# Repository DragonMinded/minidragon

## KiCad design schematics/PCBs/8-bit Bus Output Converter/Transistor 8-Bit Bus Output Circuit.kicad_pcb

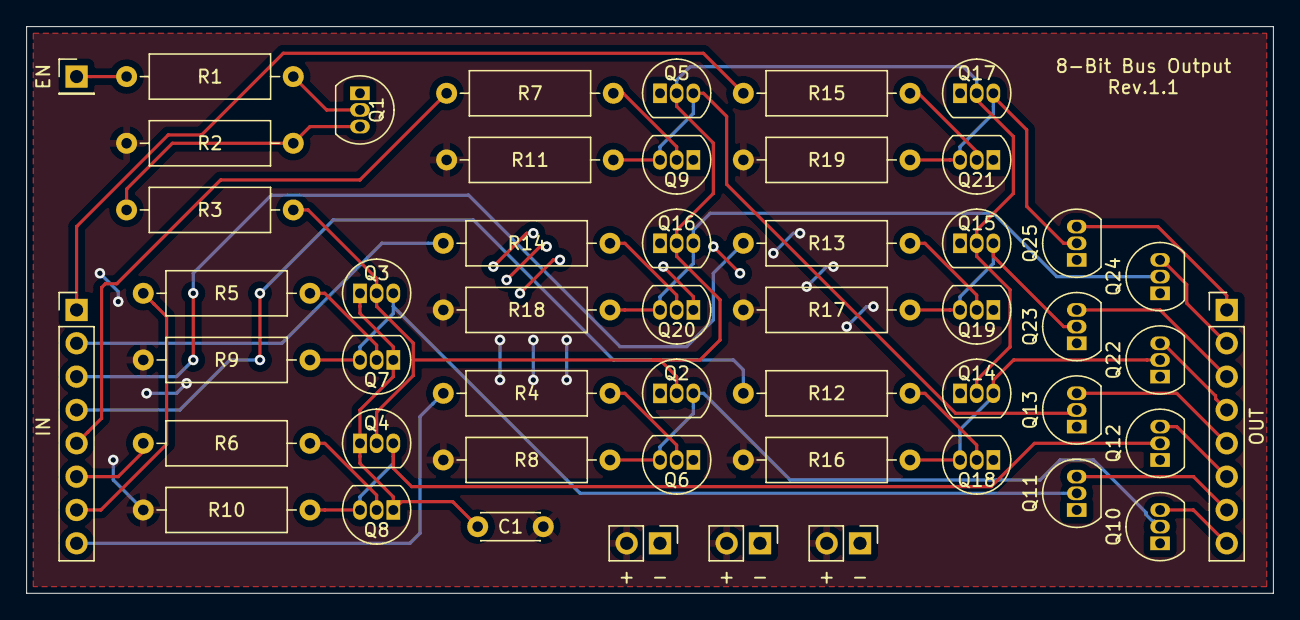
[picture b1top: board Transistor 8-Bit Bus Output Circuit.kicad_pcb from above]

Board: 2 copper layers, 95.0 x 43.2 mm, 51 parts (0 on the bottom side), 38 nets.

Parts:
C1: 0.1uF; C_Disc_D4.3mm_W1.9mm_P5.00mm
J1: EN; PinHeader_1x01_P2.54mm_Vertical
J2: IN; PinHeader_1x08_P2.54mm_Vertical
J3: OUT; PinHeader_1x08_P2.54mm_Vertical
J4, J5, J6: Power; PinHeader_1x02_P2.54mm_Vertical
Q1, Q2, Q3, Q4, Q5, Q6, Q7, Q8, Q9, Q10, Q11, Q12, Q13, Q14, Q15, Q16, Q17, Q18, Q19, Q20, Q21, Q22, Q23, Q24, Q25: 2N2222; TO-92_Inline
R1, R4, R5, R6, R7, R12, R13, R14, R15: 10K; R_Axial_DIN0309_L9.0mm_D3.2mm_P12.70mm_Horizontal
R2, R8, R9, R10, R11, R16, R17, R18, R19: 1K; R_Axial_DIN0309_L9.0mm_D3.2mm_P12.70mm_Horizontal
R3: 100; R_Axial_DIN0309_L9.0mm_D3.2mm_P12.70mm_Horizontal

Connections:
GND: C1.2, J4.1, J5.1, J6.1, Q1.1 (E), Q2.1 (E), Q3.1 (E), Q4.1 (E), Q5.1 (E), Q6.1 (E), Q7.1 (E), Q8.1 (E), Q9.1 (E), Q10.1 (E), Q11.1 (E), Q12.1 (E), Q13.1 (E), Q14.1 (E), Q15.1 (E), Q16.1 (E), Q17.1 (E), Q18.1 (E), Q19.1 (E), Q20.1 (E), Q21.1 (E), Q22.1 (E), Q23.1 (E), Q24.1 (E), Q25.1 (E)
unnamed: J1.1, R1.2
unnamed: J2.1, R15.2
unnamed: J2.2, R14.2
unnamed: J2.3, R13.2
unnamed: J2.4, R12.2
unnamed: J2.5, R7.2
unnamed: J2.6, R6.2
unnamed: J2.7, R5.2
unnamed: J2.8, R4.2
unnamed: J3.1, Q25.3 (C)
unnamed: J3.2, Q24.3 (C)
unnamed: J3.3, Q23.3 (C)
unnamed: J3.4, Q22.3 (C)
unnamed: J3.5, Q13.3 (C)
unnamed: J3.6, Q12.3 (C)
unnamed: J3.7, Q11.3 (C)
unnamed: J3.8, Q10.3 (C)
unnamed: Q1.2 (B), R1.1
unnamed: Q1.3 (C), R2.1, R3.2
unnamed: Q6.2 (B), R4.1
unnamed: Q7.2 (B), R5.1
unnamed: Q8.2 (B), R6.1
unnamed: Q9.2 (B), R7.1
unnamed: Q2.3 (C), Q6.3 (C), Q10.2 (B), R8.1
unnamed: Q3.3 (C), Q7.3 (C), Q11.2 (B), R9.1
unnamed: Q4.3 (C), Q8.3 (C), Q12.2 (B), R10.1
unnamed: Q5.3 (C), Q9.3 (C), Q13.2 (B), R11.1
unnamed: Q2.2 (B), Q3.2 (B), Q4.2 (B), Q5.2 (B), Q14.2 (B), Q15.2 (B), Q16.2 (B), Q17.2 (B), R3.1
unnamed: Q14.3 (C), Q18.3 (C), Q22.2 (B), R16.1
unnamed: Q15.3 (C), Q19.3 (C), Q23.2 (B), R17.1
unnamed: Q16.3 (C), Q20.3 (C), Q24.2 (B), R18.1
unnamed: Q17.3 (C), Q21.3 (C), Q25.2 (B), R19.1
unnamed: Q18.2 (B), R12.1
unnamed: Q19.2 (B), R13.1
unnamed: Q20.2 (B), R14.1
unnamed: Q21.2 (B), R15.1
VCC: C1.1, J4.2, J5.2, J6.2, R2.2, R8.2, R9.2, R10.2, R11.2, R16.2, R17.2, R18.2, R19.2

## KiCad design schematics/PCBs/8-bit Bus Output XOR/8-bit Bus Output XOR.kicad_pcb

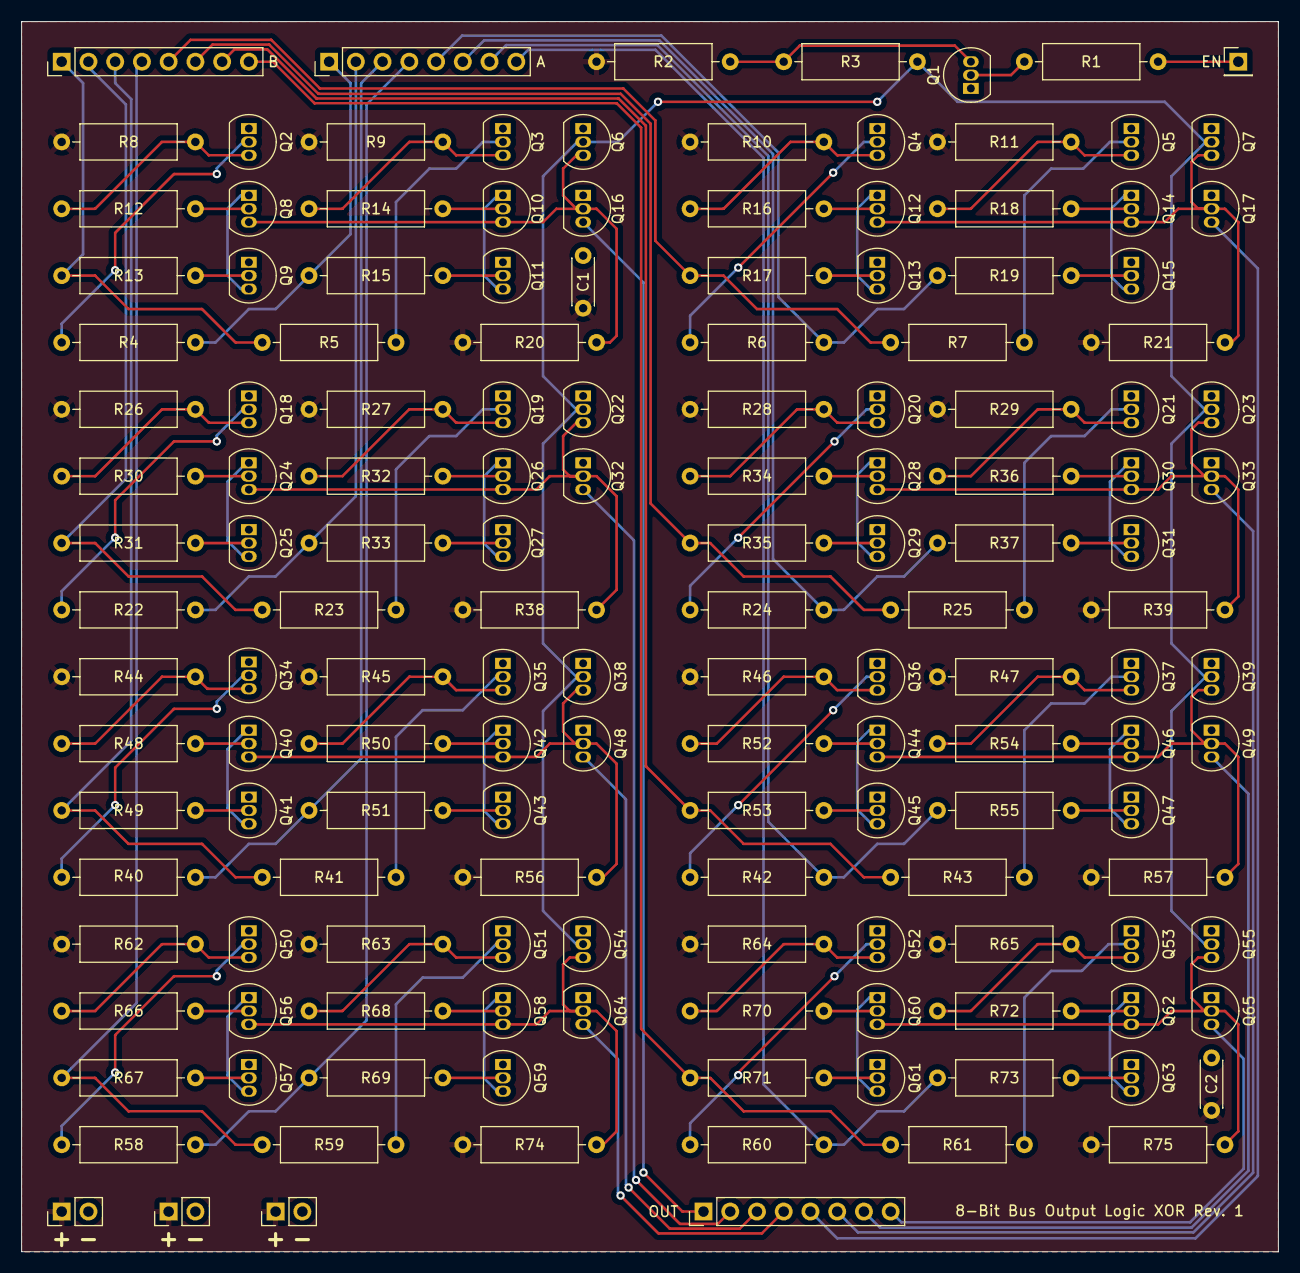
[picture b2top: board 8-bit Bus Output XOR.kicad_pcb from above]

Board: 2 copper layers, 119.4 x 116.8 mm, 149 parts (0 on the bottom side), 118 nets.

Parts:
C1, C2: 0.1uF; C_Disc_D4.3mm_W1.9mm_P5.00mm
J1: EN; PinHeader_1x01_P2.54mm_Vertical
J2: A; PinHeader_1x08_P2.54mm_Vertical
J3: B; PinHeader_1x08_P2.54mm_Vertical
J4: OUT; PinHeader_1x08_P2.54mm_Vertical
J5, J6, J7: POWER; PinHeader_1x02_P2.54mm_Vertical
Q1, Q2, Q3, Q4, Q5, Q6, Q7, Q8, Q9, Q10, Q11, Q12, Q13, Q14, Q15, Q16, Q17, Q18, Q19, Q20, Q21, Q22, Q23, Q24, Q25, Q26, Q27, Q28, Q29, Q30, Q31, Q32, Q33, Q34, Q35, Q36, Q37, Q38, Q39, Q40, Q41, Q42, Q43, Q44, Q45, Q46, Q47, Q48, Q49, Q50, Q51, Q52, Q53, Q54, Q55, Q56, Q57, Q58, Q59, Q60, Q61, Q62, Q63, Q64, Q65: 2N2222; TO-92_Inline
R1, R4, R5, R6, R7, R12, R13, R14, R15, R16, R17, R18, R19, R22, R23, R24, R25, R30, R31, R32, R33, R34, R35, R36, R37, R40, R41, R42, R43, R48, R49, R50, R51, R52, R53, R54, R55, R58, R59, R60, R61, R66, R67, R68, R69, R70, R71, R72, R73: 10K; R_Axial_DIN0309_L9.0mm_D3.2mm_P12.70mm_Horizontal
R2, R8, R9, R10, R11, R20, R21, R26, R27, R28, R29, R38, R39, R44, R45, R46, R47, R56, R57, R62, R63, R64, R65, R74, R75: 1K; R_Axial_DIN0309_L9.0mm_D3.2mm_P12.70mm_Horizontal
R3: 100; R_Axial_DIN0309_L9.0mm_D3.2mm_P12.70mm_Horizontal

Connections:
/A1: J2.1, R4.2, R15.2
/A2: J2.2, R22.2, R33.2
/A3: J2.3, R40.2, R51.2
/A4: J2.4, R58.2, R69.2
/A5: J2.5, R6.2, R19.2
/A6: J2.6, R24.2, R37.2
/A7: J2.7, R42.2, R55.2
/A8: J2.8, R60.2, R73.2
/B1: J3.1, R5.2, R13.2
/B2: J3.2, R23.2, R31.2
/B3: J3.3, R41.2, R49.2
/B4: J3.4, R59.2, R67.2
/B5: J3.5, R7.2, R17.2
/B6: J3.6, R25.2, R35.2
/B7: J3.7, R43.2, R53.2
/B8: J3.8, R61.2, R71.2
/EN_INT: Q6.2 (B), Q7.2 (B), Q22.2 (B), Q23.2 (B), Q38.2 (B), Q39.2 (B), Q54.2 (B), Q55.2 (B), R3.1
/O1: J4.1, Q16.3 (C)
/O2: J4.2, Q32.3 (C)
/O3: J4.3, Q48.3 (C)
/O4: J4.4, Q64.3 (C)
/O5: J4.5, Q17.3 (C)
/O6: J4.6, Q33.3 (C)
/O7: J4.7, Q49.3 (C)
/O8: J4.8, Q65.3 (C)
GND: C1.2, C2.2, J5.2, J6.2, J7.2, Q1.1 (E), Q2.1 (E), Q3.1 (E), Q4.1 (E), Q5.1 (E), Q6.1 (E), Q7.1 (E), Q9.1 (E), Q11.1 (E), Q13.1 (E), Q15.1 (E), Q16.1 (E), Q17.1 (E), Q18.1 (E), Q19.1 (E), Q20.1 (E), Q21.1 (E), Q22.1 (E), Q23.1 (E), Q25.1 (E), Q27.1 (E), Q29.1 (E), Q31.1 (E), Q32.1 (E), Q33.1 (E), Q34.1 (E), Q35.1 (E), Q36.1 (E), Q37.1 (E), Q38.1 (E), Q39.1 (E), Q41.1 (E), Q43.1 (E), Q45.1 (E), Q47.1 (E), Q48.1 (E), Q49.1 (E), Q50.1 (E), Q51.1 (E), Q52.1 (E), Q53.1 (E), Q54.1 (E), Q55.1 (E), Q57.1 (E), Q59.1 (E), Q61.1 (E), Q63.1 (E), Q64.1 (E), Q65.1 (E)
unnamed: J1.1, R1.2
unnamed: Q1.2 (B), R1.1
unnamed: Q1.3 (C), R2.1, R3.2
unnamed: Q2.2 (B), R4.1
unnamed: Q2.3 (C), R8.2, R12.2
unnamed: Q3.2 (B), R5.1
unnamed: Q3.3 (C), R9.2, R14.2
unnamed: Q4.2 (B), R6.1
unnamed: Q4.3 (C), R10.2, R16.2
unnamed: Q5.2 (B), R7.1
unnamed: Q5.3 (C), R11.2, R18.2
unnamed: Q8.2 (B), R12.1
unnamed: Q8.1 (E), Q9.3 (C)
unnamed: Q9.2 (B), R13.1
unnamed: Q10.2 (B), R14.1
unnamed: Q6.3 (C), Q8.3 (C), Q10.3 (C), Q16.2 (B), R20.1
unnamed: Q10.1 (E), Q11.3 (C)
unnamed: Q11.2 (B), R15.1
unnamed: Q12.2 (B), R16.1
unnamed: Q7.3 (C), Q12.3 (C), Q14.3 (C), Q17.2 (B), R21.1
unnamed: Q12.1 (E), Q13.3 (C)
unnamed: Q13.2 (B), R17.1
unnamed: Q14.2 (B), R18.1
unnamed: Q14.1 (E), Q15.3 (C)
unnamed: Q15.2 (B), R19.1
unnamed: Q18.2 (B), R22.1
unnamed: Q18.3 (C), R26.2, R30.2
unnamed: Q19.2 (B), R23.1
unnamed: Q19.3 (C), R27.2, R32.2
unnamed: Q20.2 (B), R24.1
unnamed: Q20.3 (C), R28.2, R34.2
unnamed: Q21.2 (B), R25.1
unnamed: Q21.3 (C), R29.2, R36.2
unnamed: Q22.3 (C), Q24.3 (C), Q26.3 (C), Q32.2 (B), R38.1
unnamed: Q23.3 (C), Q28.3 (C), Q30.3 (C), Q33.2 (B), R39.1
unnamed: Q24.2 (B), R30.1
unnamed: Q24.1 (E), Q25.3 (C)
unnamed: Q25.2 (B), R31.1
unnamed: Q26.2 (B), R32.1
unnamed: Q26.1 (E), Q27.3 (C)
unnamed: Q27.2 (B), R33.1
unnamed: Q28.2 (B), R34.1
unnamed: Q28.1 (E), Q29.3 (C)
unnamed: Q29.2 (B), R35.1
unnamed: Q30.2 (B), R36.1
unnamed: Q30.1 (E), Q31.3 (C)
unnamed: Q31.2 (B), R37.1
unnamed: Q34.2 (B), R40.1
unnamed: Q34.3 (C), R44.2, R48.2
unnamed: Q35.2 (B), R41.1
unnamed: Q35.3 (C), R45.2, R50.2
unnamed: Q36.2 (B), R42.1
unnamed: Q36.3 (C), R46.2, R52.2
unnamed: Q37.2 (B), R43.1
unnamed: Q37.3 (C), R47.2, R54.2
unnamed: Q38.3 (C), Q40.3 (C), Q42.3 (C), Q48.2 (B), R56.1
unnamed: Q39.3 (C), Q44.3 (C), Q46.3 (C), Q49.2 (B), R57.1
unnamed: Q40.2 (B), R48.1
unnamed: Q40.1 (E), Q41.3 (C)
unnamed: Q41.2 (B), R49.1
unnamed: Q42.2 (B), R50.1
unnamed: Q42.1 (E), Q43.3 (C)
unnamed: Q43.2 (B), R51.1
unnamed: Q44.2 (B), R52.1
unnamed: Q44.1 (E), Q45.3 (C)
unnamed: Q45.2 (B), R53.1
unnamed: Q46.2 (B), R54.1
unnamed: Q46.1 (E), Q47.3 (C)
unnamed: Q47.2 (B), R55.1
unnamed: Q50.2 (B), R58.1
unnamed: Q50.3 (C), R62.2, R66.2
unnamed: Q51.2 (B), R59.1
unnamed: Q51.3 (C), R63.2, R68.2
unnamed: Q52.2 (B), R60.1
unnamed: Q52.3 (C), R64.2, R70.2
unnamed: Q53.2 (B), R61.1
unnamed: Q53.3 (C), R65.2, R72.2
unnamed: Q54.3 (C), Q56.3 (C), Q58.3 (C), Q64.2 (B), R74.1
unnamed: Q55.3 (C), Q60.3 (C), Q62.3 (C), Q65.2 (B), R75.1
unnamed: Q56.2 (B), R66.1
unnamed: Q56.1 (E), Q57.3 (C)
unnamed: Q57.2 (B), R67.1
unnamed: Q58.2 (B), R68.1
unnamed: Q58.1 (E), Q59.3 (C)
unnamed: Q59.2 (B), R69.1
unnamed: Q60.2 (B), R70.1
unnamed: Q60.1 (E), Q61.3 (C)
unnamed: Q61.2 (B), R71.1
unnamed: Q62.2 (B), R72.1
unnamed: Q62.1 (E), Q63.3 (C)
unnamed: Q63.2 (B), R73.1
VCC: C1.1, C2.1, J5.1, J6.1, J7.1, R2.2, R8.1, R9.1, R10.1, R11.1, R20.2, R21.2, R26.1, R27.1, R28.1, R29.1, R38.2, R39.2, R44.1, R45.1, R46.1, R47.1, R56.2, R57.2, R62.1, R63.1, R64.1, R65.1, R74.2, R75.2

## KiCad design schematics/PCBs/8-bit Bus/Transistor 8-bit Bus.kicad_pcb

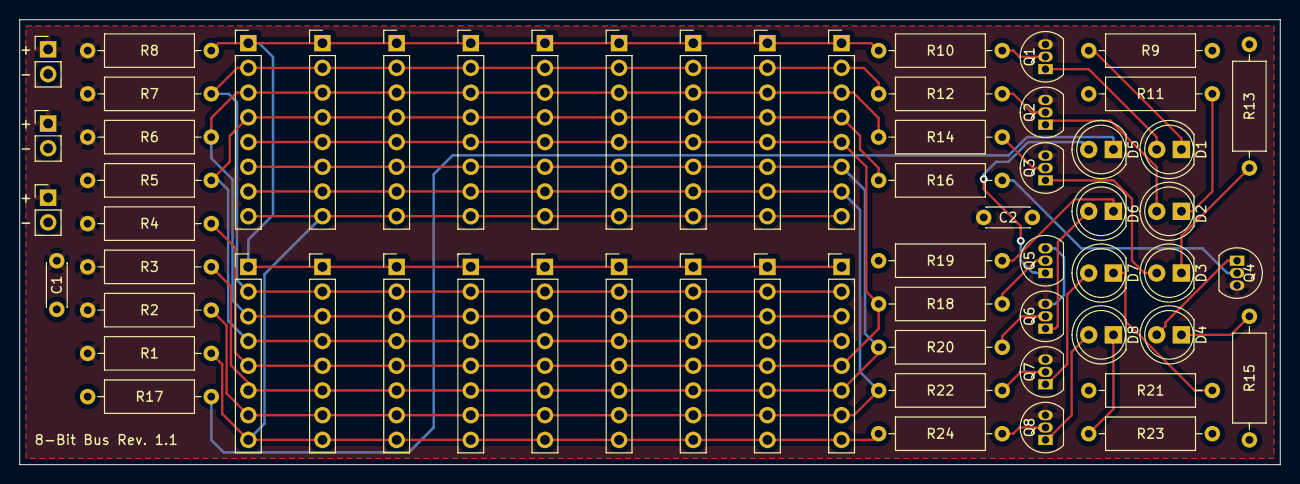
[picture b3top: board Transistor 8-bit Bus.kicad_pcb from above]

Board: 2 copper layers, 129.5 x 45.7 mm, 63 parts (0 on the bottom side), 34 nets.

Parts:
C1, C2: 0.1uF; C_Disc_D4.3mm_W1.9mm_P5.00mm
D1, D2, D3, D4, D5, D6, D7, D8: LED; LED_D5.0mm
J1, J2, J5: Power; PinHeader_1x02_P2.54mm_Vertical
J3, J4, J6, J7, J8, J9, J10, J11, J12, J13, J14, J15, J16, J17, J18, J19, J20, J21: Bus; PinHeader_1x08_P2.54mm_Vertical
Q1, Q2, Q3, Q4, Q5, Q6, Q7, Q8: 2N2222; TO-92_Inline
R1, R2, R3, R4, R5, R6, R7, R8: 100; R_Axial_DIN0309_L9.0mm_D3.2mm_P12.70mm_Horizontal
R9, R10, R11, R12, R13, R14, R15, R16, R17, R18, R19, R20, R21, R22, R23, R24: 10K; R_Axial_DIN0309_L9.0mm_D3.2mm_P12.70mm_Horizontal

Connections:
/1: J3.1, J4.1, J6.1, J7.1, J8.1, J9.1, J10.1, J11.1, J12.1, J13.1, J14.1, J15.1, J16.1, J17.1, J18.1, J19.1, J20.1, J21.1, R8.2, R10.1
/2: J3.2, J4.2, J6.2, J7.2, J8.2, J9.2, J10.2, J11.2, J12.2, J13.2, J14.2, J15.2, J16.2, J17.2, J18.2, J19.2, J20.2, J21.2, R7.2, R12.1
/3: J3.3, J4.3, J6.3, J7.3, J8.3, J9.3, J10.3, J11.3, J12.3, J13.3, J14.3, J15.3, J16.3, J17.3, J18.3, J19.3, J20.3, J21.3, R6.2, R14.1
/4: J3.4, J4.4, J6.4, J7.4, J8.4, J9.4, J10.4, J11.4, J12.4, J13.4, J14.4, J15.4, J16.4, J17.4, J18.4, J19.4, J20.4, J21.4, R5.2, R16.1
/5: J3.5, J4.5, J6.5, J7.5, J8.5, J9.5, J10.5, J11.5, J12.5, J13.5, J14.5, J15.5, J16.5, J17.5, J18.5, J19.5, J20.5, J21.5, R4.2, R18.1
/6: J3.6, J4.6, J6.6, J7.6, J8.6, J9.6, J10.6, J11.6, J12.6, J13.6, J14.6, J15.6, J16.6, J17.6, J18.6, J19.6, J20.6, J21.6, R3.2, R20.1
/7: J3.7, J4.7, J6.7, J7.7, J8.7, J9.7, J10.7, J11.7, J12.7, J13.7, J14.7, J15.7, J16.7, J17.7, J18.7, J19.7, J20.7, J21.7, R2.2, R22.1
/8: J3.8, J4.8, J6.8, J7.8, J8.8, J9.8, J10.8, J11.8, J12.8, J13.8, J14.8, J15.8, J16.8, J17.8, J18.8, J19.8, J20.8, J21.8, R1.2, R24.1
GND: C1.2, C2.2, J1.2, J2.2, J5.2, R9.2, R11.2, R13.2, R15.2, R17.2, R19.2, R21.2, R23.2
unnamed: D1.2 (A), Q1.1 (E)
unnamed: D1.1 (K), R9.1
unnamed: D2.2 (A), Q2.1 (E)
unnamed: D2.1 (K), R11.1
unnamed: D3.2 (A), Q3.1 (E)
unnamed: D3.1 (K), R13.1
unnamed: D4.2 (A), Q4.1 (E)
unnamed: D4.1 (K), R15.1
unnamed: D5.2 (A), Q5.1 (E)
unnamed: D5.1 (K), R17.1
unnamed: D6.2 (A), Q6.1 (E)
unnamed: D6.1 (K), R19.1
unnamed: D7.2 (A), Q7.1 (E)
unnamed: D7.1 (K), R21.1
unnamed: D8.2 (A), Q8.1 (E)
unnamed: D8.1 (K), R23.1
unnamed: Q1.2 (B), R10.2
unnamed: Q2.2 (B), R12.2
unnamed: Q3.2 (B), R14.2
unnamed: Q4.2 (B), R16.2
unnamed: Q5.2 (B), R18.2
unnamed: Q6.2 (B), R20.2
unnamed: Q7.2 (B), R22.2
unnamed: Q8.2 (B), R24.2
VCC: C1.1, C2.1, J1.1, J2.1, J5.1, Q1.3 (C), Q2.3 (C), Q3.3 (C), Q4.3 (C), Q5.3 (C), Q6.3 (C), Q7.3 (C), Q8.3 (C), R1.1, R2.1, R3.1, R4.1, R5.1, R6.1, R7.1, R8.1

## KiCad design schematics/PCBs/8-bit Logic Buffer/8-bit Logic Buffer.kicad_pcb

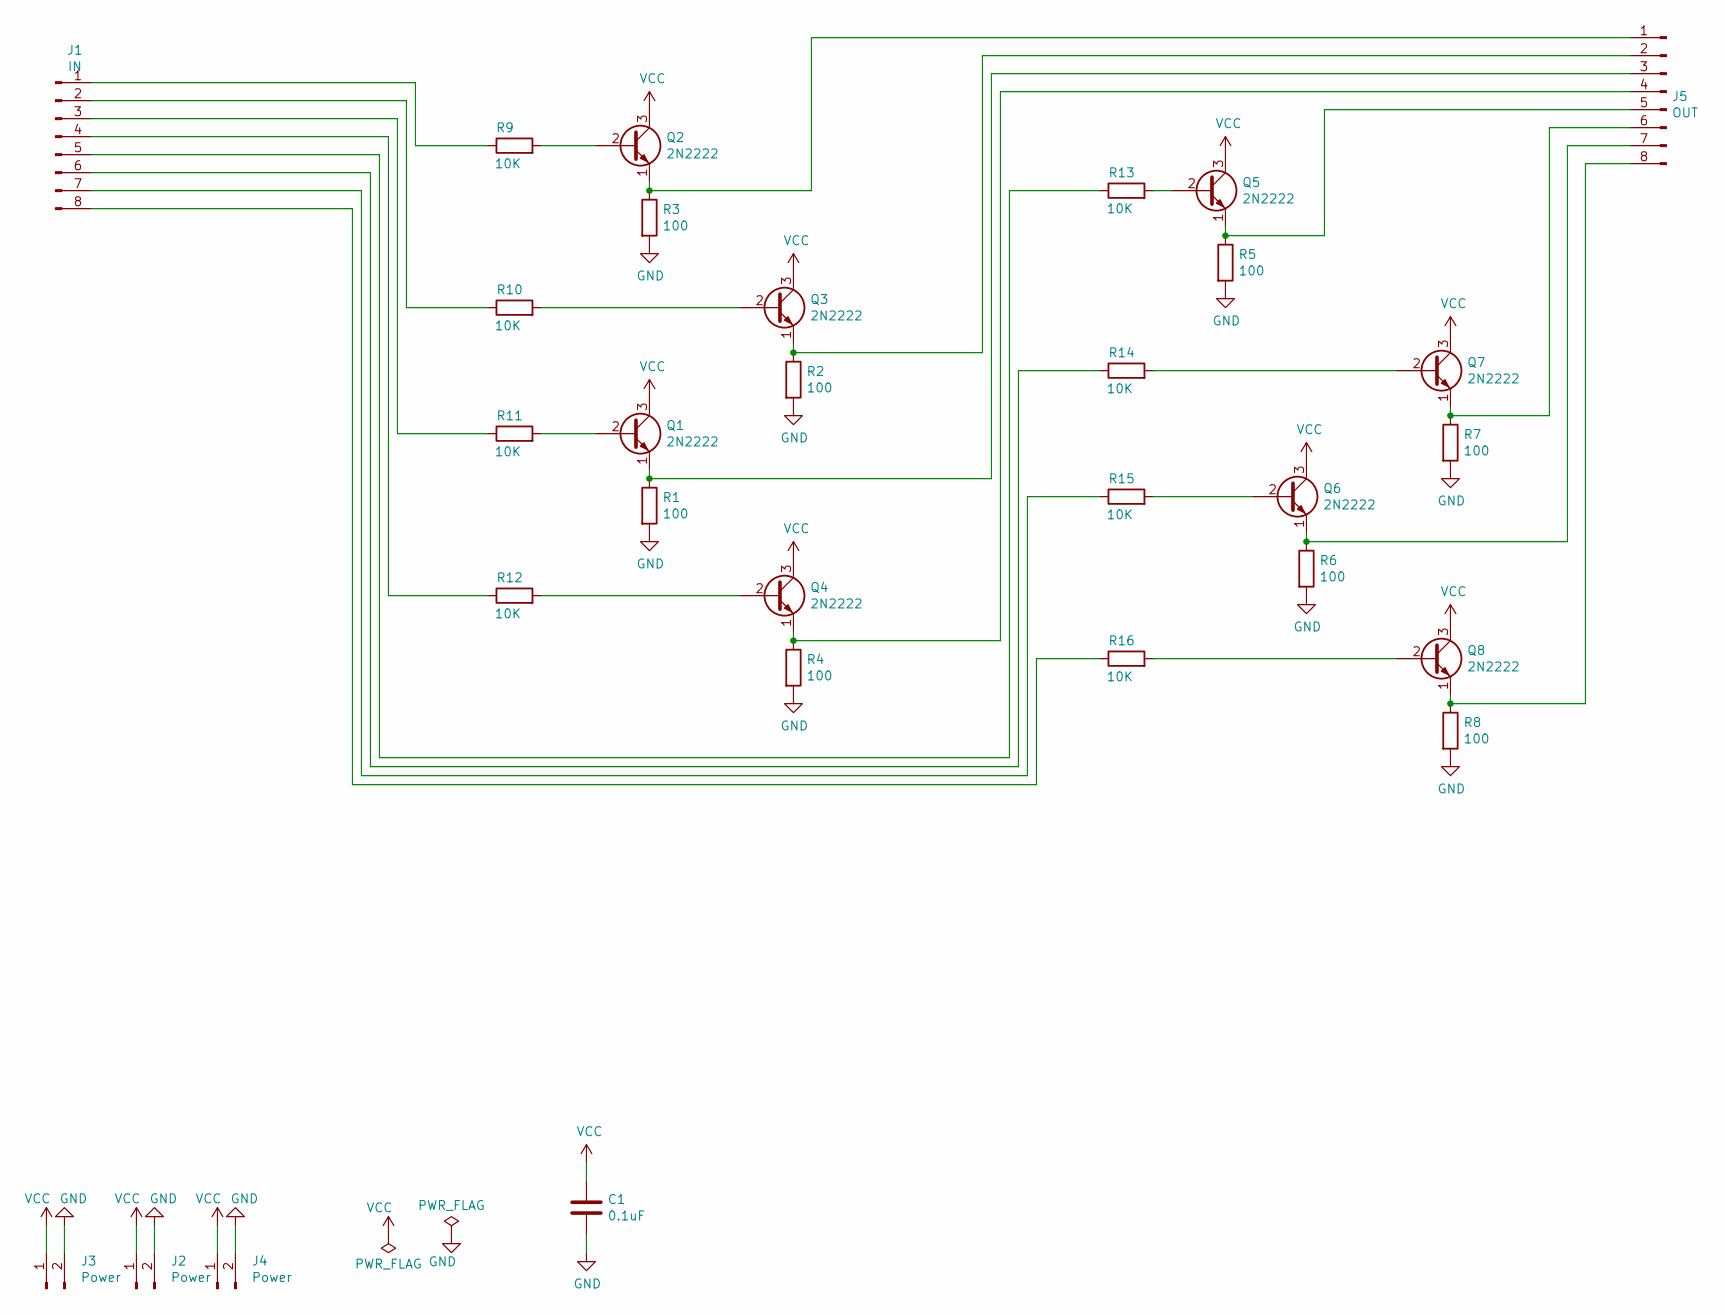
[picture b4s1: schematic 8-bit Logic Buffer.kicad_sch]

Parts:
C1: 0.1uF; C_Disc_D4.3mm_W1.9mm_P5.00mm
J1: IN; PinHeader_1x08_P2.54mm_Vertical
J2, J3, J4: Power; PinHeader_1x02_P2.54mm_Vertical
J5: OUT; PinHeader_1x08_P2.54mm_Vertical
Q1, Q2, Q3, Q4, Q5, Q6, Q7, Q8: 2N2222; TO-92_Inline
R1, R2, R3, R4, R5, R6, R7, R8: 100; R_Axial_DIN0309_L9.0mm_D3.2mm_P12.70mm_Horizontal
R9, R10, R11, R12, R13, R14, R15, R16: 10K; R_Axial_DIN0309_L9.0mm_D3.2mm_P12.70mm_Horizontal

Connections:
GND: C1.2, J2.2, J3.2, J4.2, R1.2, R2.2, R3.2, R4.2, R5.2, R6.2, R7.2, R8.2
unnamed: J1.1, R9.1
unnamed: J1.2, R10.1
unnamed: J1.3, R11.1
unnamed: J1.4, R12.1
unnamed: J1.5, R13.1
unnamed: J1.6, R14.1
unnamed: J1.7, R15.1
unnamed: J1.8, R16.1
unnamed: J5.1, Q2.1 (E), R3.1
unnamed: J5.2, Q3.1 (E), R2.1
unnamed: J5.3, Q1.1 (E), R1.1
unnamed: J5.4, Q4.1 (E), R4.1
unnamed: J5.5, Q5.1 (E), R5.1
unnamed: J5.6, Q7.1 (E), R7.1
unnamed: J5.7, Q6.1 (E), R6.1
unnamed: J5.8, Q8.1 (E), R8.1
unnamed: Q1.2 (B), R11.2
unnamed: Q2.2 (B), R9.2
unnamed: Q3.2 (B), R10.2
unnamed: Q4.2 (B), R12.2
unnamed: Q5.2 (B), R13.2
unnamed: Q6.2 (B), R15.2
unnamed: Q7.2 (B), R14.2
unnamed: Q8.2 (B), R16.2
VCC: C1.1, J2.1, J3.1, J4.1, Q1.3 (C), Q2.3 (C), Q3.3 (C), Q4.3 (C), Q5.3 (C), Q6.3 (C), Q7.3 (C), Q8.3 (C)

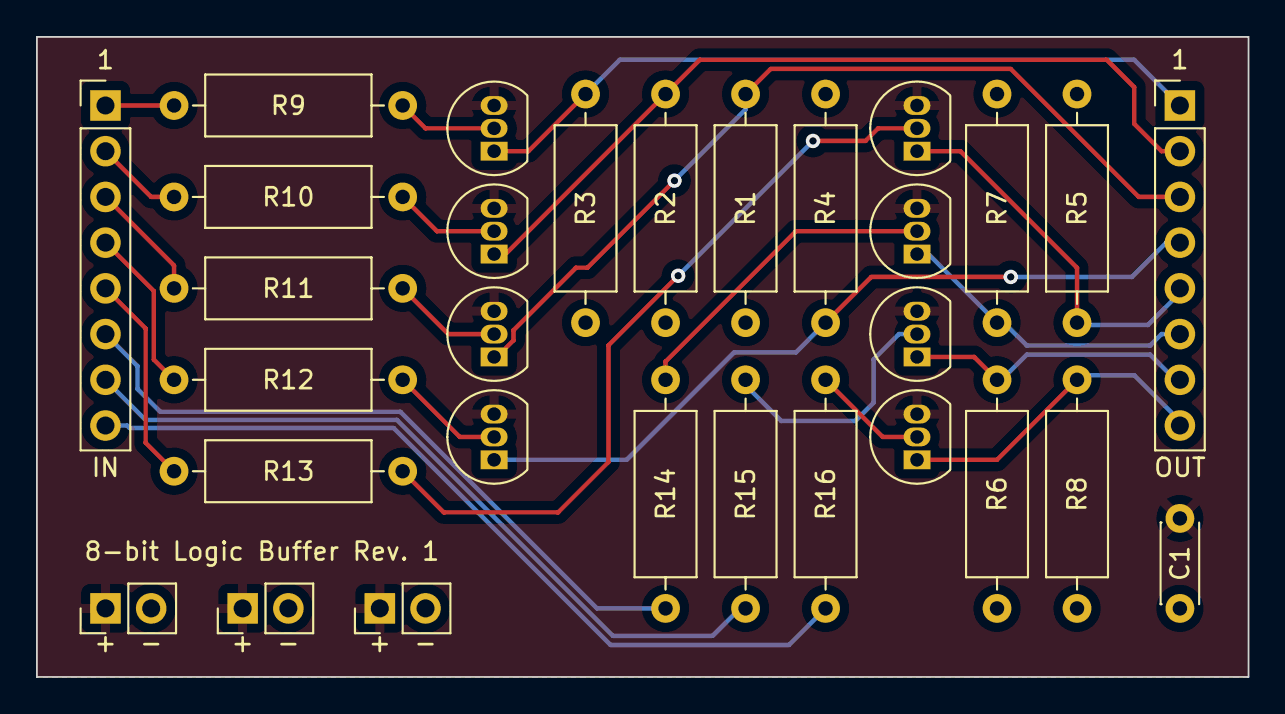
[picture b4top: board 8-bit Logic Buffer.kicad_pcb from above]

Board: 2 copper layers, 67.3 x 35.6 mm, 30 parts (0 on the bottom side), 26 nets.

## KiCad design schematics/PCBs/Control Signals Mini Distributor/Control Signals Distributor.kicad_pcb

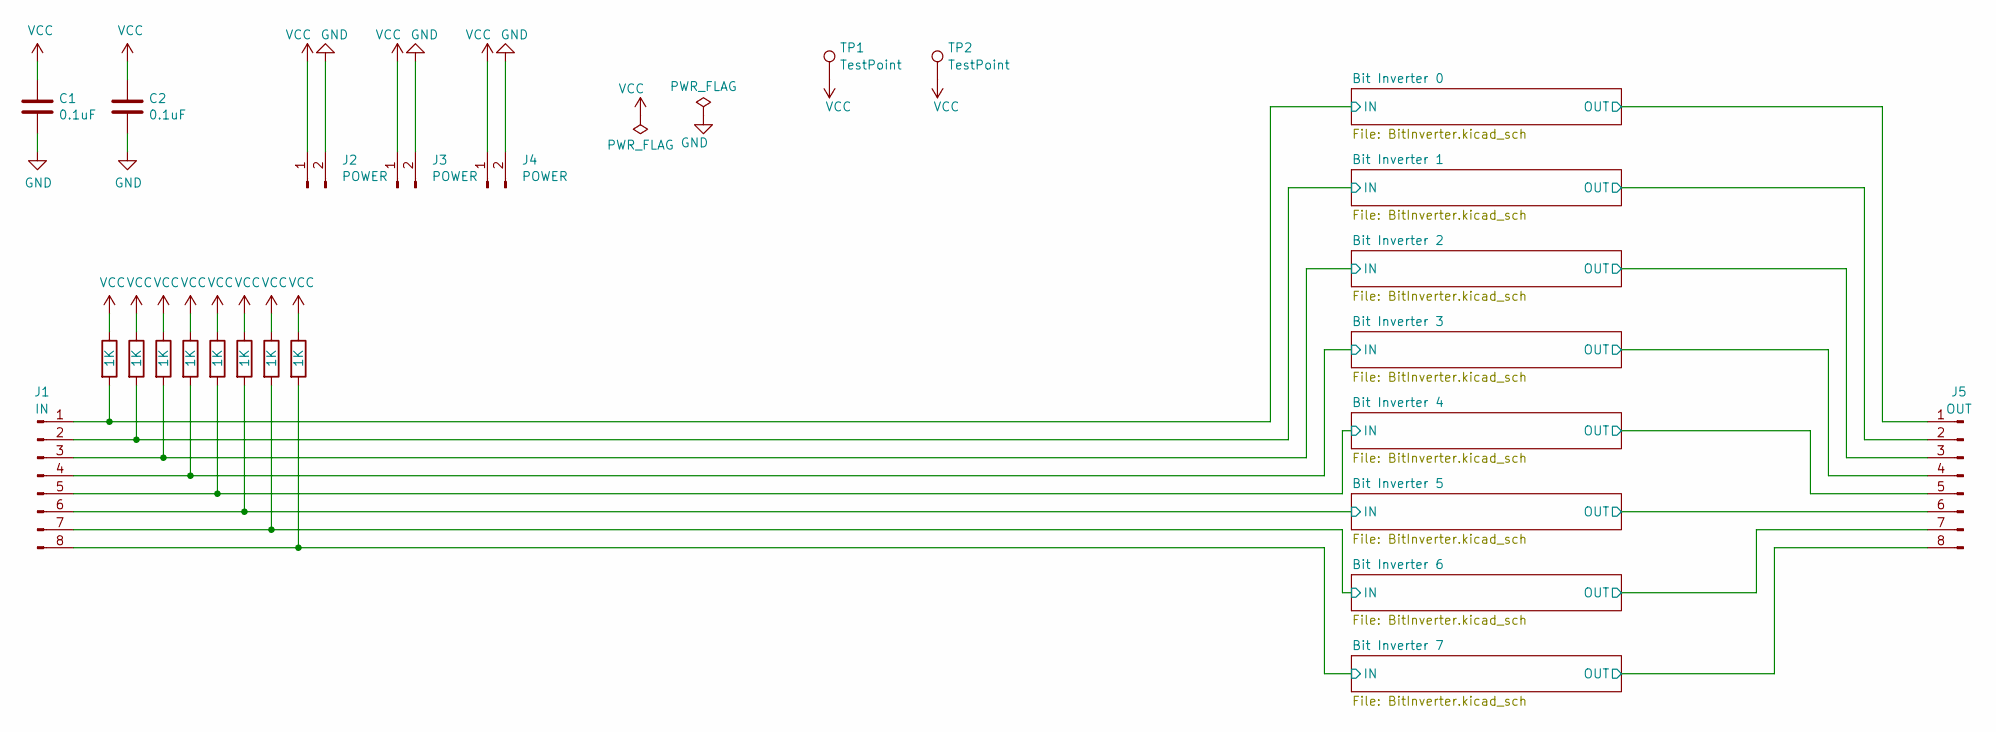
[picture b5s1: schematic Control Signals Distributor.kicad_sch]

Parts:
C1, C2: 0.1uF; C_Disc_D4.3mm_W1.9mm_P5.00mm
J1: IN; PinHeader_1x08_P2.54mm_Vertical
J2, J3, J4: POWER; PinHeader_1x02_P2.54mm_Vertical
J5: OUT; PinHeader_1x08_P2.54mm_Vertical
R1, R2, R3, R4, R5, R6, R7, R8: 1K; R_Axial_DIN0309_L9.0mm_D3.2mm_P12.70mm_Horizontal
TP1, TP2: TestPoint; TestPoint_THTPad_D2.0mm_Drill1.0mm

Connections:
/Bit Inverter 0/IN: J1.1, R1.2; also elsewhere on the board
/Bit Inverter 0/OUT: J5.1; also elsewhere on the board
/Bit Inverter 1/IN: J1.2, R2.2; also elsewhere on the board
/Bit Inverter 1/OUT: J5.2; also elsewhere on the board
/Bit Inverter 2/IN: J1.3, R3.2; also elsewhere on the board
/Bit Inverter 2/OUT: J5.3; also elsewhere on the board
/Bit Inverter 3/IN: J1.4, R4.2; also elsewhere on the board
/Bit Inverter 3/OUT: J5.4; also elsewhere on the board
/Bit Inverter 4/IN: J1.5, R5.2; also elsewhere on the board
/Bit Inverter 4/OUT: J5.5; also elsewhere on the board
/Bit Inverter 5/IN: J1.6, R6.2; also elsewhere on the board
/Bit Inverter 5/OUT: J5.6; also elsewhere on the board
/Bit Inverter 6/IN: J1.7, R7.2; also elsewhere on the board
/Bit Inverter 6/OUT: J5.7; also elsewhere on the board
/Bit Inverter 7/IN: J1.8, R8.2; also elsewhere on the board
/Bit Inverter 7/OUT: J5.8; also elsewhere on the board
GND: C1.2, C2.2, J2.2, J3.2, J4.2; also elsewhere on the board
VCC: C1.1, C2.1, J2.1, J3.1, J4.1, R1.1, R2.1, R3.1, R4.1, R5.1, R6.1, R7.1, R8.1, TP1.1, TP2.1; also elsewhere on the board

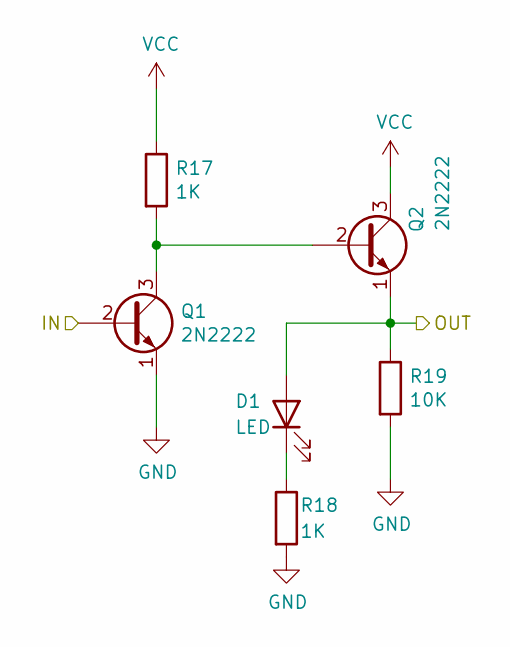
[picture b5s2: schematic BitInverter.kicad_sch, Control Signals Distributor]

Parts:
D1: LED; LED_D5.0mm
Q1, Q2: 2N2222; TO-92_Inline
R17, R18: 1K; R_Axial_DIN0309_L9.0mm_D3.2mm_P12.70mm_Horizontal
R19: 10K; R_Axial_DIN0309_L9.0mm_D3.2mm_P12.70mm_Horizontal

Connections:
/Bit Inverter 0/IN: Q1.2 (B); also elsewhere on the board
/Bit Inverter 0/OUT: D1.2 (A), Q2.1 (E), R19.1; also elsewhere on the board
GND: Q1.1 (E), R18.2, R19.2; also elsewhere on the board
unnamed: D1.1 (K), R18.1
unnamed: Q1.3 (C), Q2.2 (B), R17.2
VCC: Q2.3 (C), R17.1; also elsewhere on the board

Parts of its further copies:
D2, D3, D4, D5, D6, D7, D8: LED; LED_D5.0mm
Q3, Q4, Q5, Q6, Q7, Q8, Q9, Q10, Q11, Q12, Q13, Q14, Q15, Q16: 2N2222; TO-92_Inline
R20, R21, R23, R24, R26, R27, R29, R30, R32, R33, R35, R36, R38, R39: 1K; R_Axial_DIN0309_L9.0mm_D3.2mm_P12.70mm_Horizontal
R22, R25, R28, R31, R34, R37, R40: 10K; R_Axial_DIN0309_L9.0mm_D3.2mm_P12.70mm_Horizontal

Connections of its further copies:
/Bit Inverter 1/IN: Q3.2 (B); also elsewhere on the board
/Bit Inverter 1/OUT: D2.2 (A), Q4.1 (E), R22.1; also elsewhere on the board
/Bit Inverter 2/IN: Q5.2 (B); also elsewhere on the board
/Bit Inverter 2/OUT: D3.2 (A), Q6.1 (E), R25.1; also elsewhere on the board
/Bit Inverter 3/IN: Q7.2 (B); also elsewhere on the board
/Bit Inverter 3/OUT: D4.2 (A), Q8.1 (E), R28.1; also elsewhere on the board
/Bit Inverter 4/IN: Q9.2 (B); also elsewhere on the board
/Bit Inverter 4/OUT: D5.2 (A), Q10.1 (E), R31.1; also elsewhere on the board
/Bit Inverter 5/IN: Q11.2 (B); also elsewhere on the board
/Bit Inverter 5/OUT: D6.2 (A), Q12.1 (E), R34.1; also elsewhere on the board
/Bit Inverter 6/IN: Q13.2 (B); also elsewhere on the board
/Bit Inverter 6/OUT: D7.2 (A), Q14.1 (E), R37.1; also elsewhere on the board
/Bit Inverter 7/IN: Q15.2 (B); also elsewhere on the board
/Bit Inverter 7/OUT: D8.2 (A), Q16.1 (E), R40.1; also elsewhere on the board
GND: Q3.1 (E), Q5.1 (E), Q7.1 (E), Q9.1 (E), Q11.1 (E), Q13.1 (E), Q15.1 (E), R21.2, R22.2, R24.2, R25.2, R27.2, R28.2, R30.2, R31.2, R33.2, R34.2, R36.2, R37.2, R39.2, R40.2; also elsewhere on the board
unnamed: D2.1 (K), R21.1
unnamed: D3.1 (K), R24.1
unnamed: D4.1 (K), R27.1
unnamed: D5.1 (K), R30.1
unnamed: D6.1 (K), R33.1
unnamed: D7.1 (K), R36.1
unnamed: D8.1 (K), R39.1
unnamed: Q3.3 (C), Q4.2 (B), R20.2
unnamed: Q5.3 (C), Q6.2 (B), R23.2
unnamed: Q7.3 (C), Q8.2 (B), R26.2
unnamed: Q9.3 (C), Q10.2 (B), R29.2
unnamed: Q11.3 (C), Q12.2 (B), R32.2
unnamed: Q13.3 (C), Q14.2 (B), R35.2
unnamed: Q15.3 (C), Q16.2 (B), R38.2
VCC: Q4.3 (C), Q6.3 (C), Q8.3 (C), Q10.3 (C), Q12.3 (C), Q14.3 (C), Q16.3 (C), R20.1, R23.1, R26.1, R29.1, R32.1, R35.1, R38.1; also elsewhere on the board

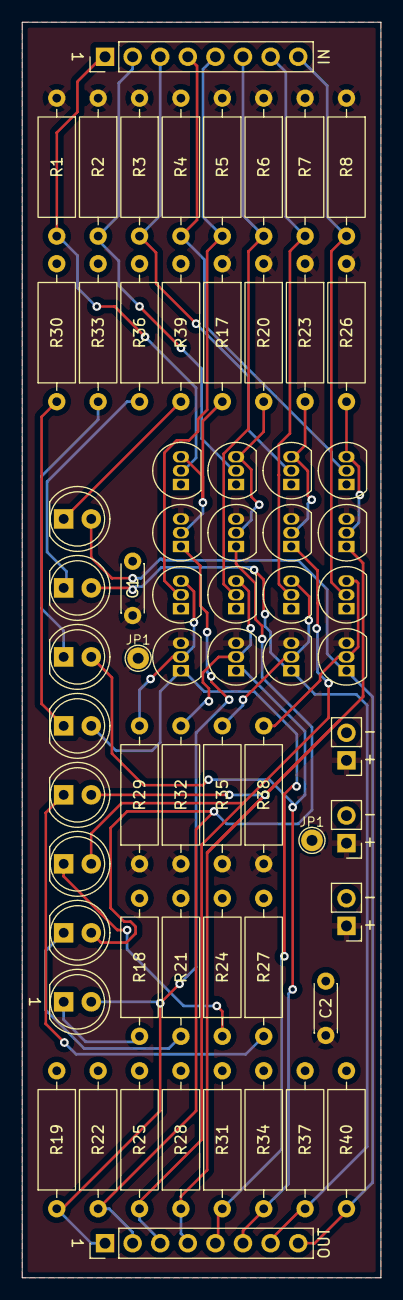
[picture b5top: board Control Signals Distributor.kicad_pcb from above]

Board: 2 copper layers, 33.0 x 115.6 mm, 65 parts (0 on the bottom side), 34 nets.

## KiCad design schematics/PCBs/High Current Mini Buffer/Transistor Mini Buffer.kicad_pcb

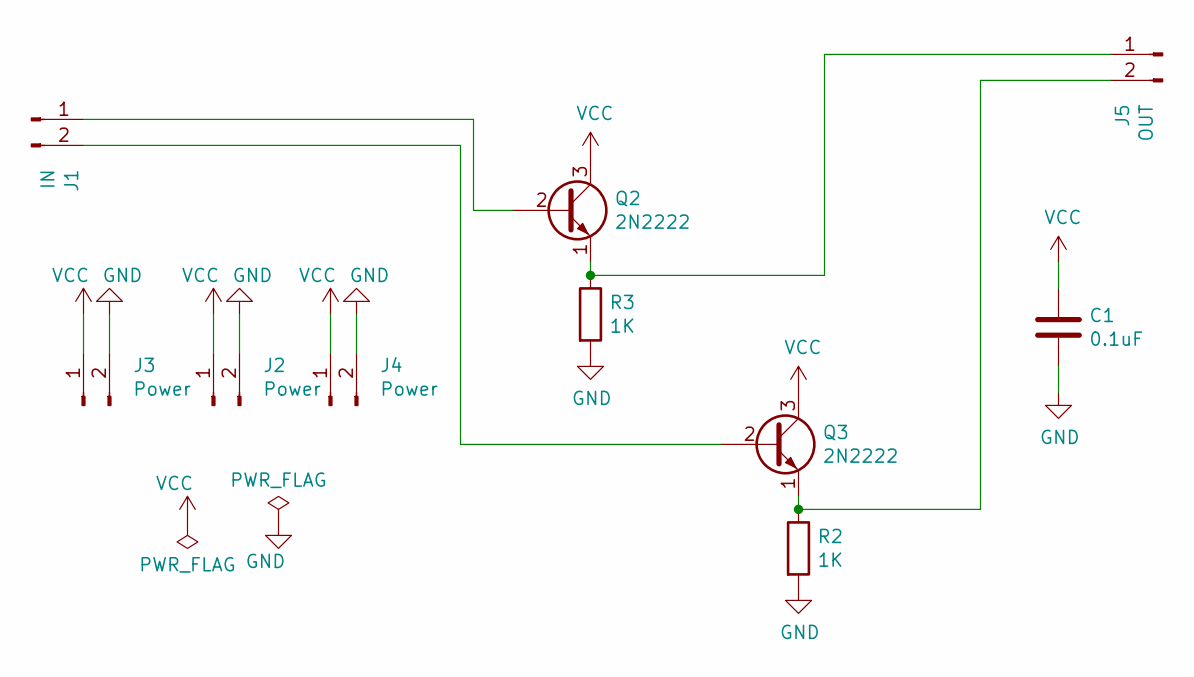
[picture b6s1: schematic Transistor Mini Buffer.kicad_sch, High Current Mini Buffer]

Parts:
C1: 0.1uF; C_Disc_D4.3mm_W1.9mm_P5.00mm
J1: IN; PinHeader_1x02_P2.54mm_Vertical
J2, J3, J4: Power; PinHeader_1x02_P2.54mm_Vertical
J5: OUT; PinHeader_1x02_P2.54mm_Vertical
Q2, Q3: 2N2222; TO-92_Inline
R2, R3: 1K; R_Axial_DIN0309_L9.0mm_D3.2mm_P12.70mm_Horizontal

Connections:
GND: C1.2, J2.2, J3.2, J4.2, R2.2, R3.2
unnamed: J1.1, Q2.2 (B)
unnamed: J1.2, Q3.2 (B)
unnamed: J5.1, Q2.1 (E), R3.1
unnamed: J5.2, Q3.1 (E), R2.1
VCC: C1.1, J2.1, J3.1, J4.1, Q2.3 (C), Q3.3 (C)

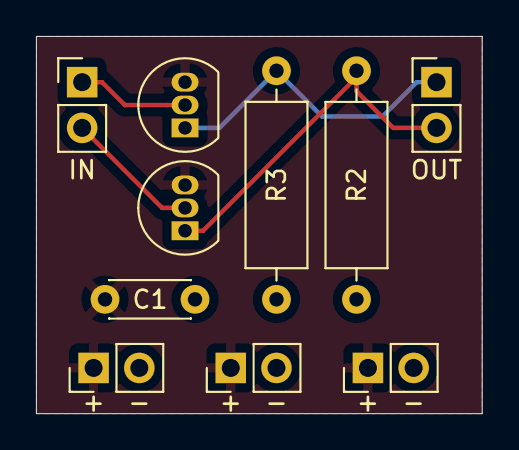
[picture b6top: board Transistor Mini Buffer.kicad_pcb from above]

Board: 2 copper layers, 24.8 x 21.0 mm, 10 parts (0 on the bottom side), 6 nets.
